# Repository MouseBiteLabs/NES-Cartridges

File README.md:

# NES-Cartridges
A collection of Nintendo Entertainment System (NES) cartridge circuit boards

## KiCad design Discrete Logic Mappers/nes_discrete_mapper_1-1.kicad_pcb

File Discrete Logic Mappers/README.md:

# Nintendo Entertainment System (NES) Discrete Mapper Cartridge

This is an updated design of my old <a href="https://mousebitelabs.com/2020/09/11/nes-reproduction-quick-guide-custom-pcb/">NES Discrete cartridge boards</a>. Functionally, this design is nearly the same as the older one, but I added compatibility for a few new mappers and expanded the available memory for some mapper types, and under the hood I have ported the project over from Eagle to KiCad and heavily cleaned up the schematic and some of the trace routings. This version is also fully open source!

This circuit board can be used to make most NES cartridges that rely on discrete logic chips to operate. These boards are most common in the earlier NES releases. The following mapper types are supported (click the link to view the games that use that specific mapper):

| Board        | Mapper | Example Game                  | Database Link                                                                                  |
| ------------ | ------ | ----------------------------- | ---------------------------------------------------------------------------------------------- |
| NROM         | 0      | Balloon Fight                 | [https://nescartdb.com/search/advanced?ines=0](https://nescartdb.com/search/advanced?ines=0)   |
| UxROM        | 2      | Castlevania                   | [https://nescartdb.com/search/advanced?ines=2](https://nescartdb.com/search/advanced?ines=2)   |
| CNROM        | 3      | Paperboy                      | [https://nescartdb.com/search/advanced?ines=3](https://nescartdb.com/search/advanced?ines=3)   |
| AxROM        | 7      | Battletoads                   | [https://nescartdb.com/search/advanced?ines=7](https://nescartdb.com/search/advanced?ines=7)   |
| Color Dreams | 11     | Bible Adventures              | [https://nescartdb.com/search/advanced?ines=11](https://nescartdb.com/search/advanced?ines=11) |
| BNROM        | 34     | Deadly Towers                 | [https://nescartdb.com/search/advanced?ines=34](https://nescartdb.com/search/advanced?ines=34) |
| GNROM        | 66     | Super Mario Bros. / Duck Hunt | [https://nescartdb.com/search/advanced?ines=66](https://nescartdb.com/search/advanced?ines=66) |

There are a handful of more obscure mappers supported as well:

| Board            | Mapper | Example Game        | Wiki Link                                                                                  |
| ---------------- | ------ | ------------------- | ------------------------------------------------------------------------------------------ |
| CNROM (Panesian) | 3      | Bubble Bath Babes   | https://www.nesdev.org/wiki/Oversize                                                       |
| NINA-03/-06      | 79     | Krazy Kreatures     | https://www.nesdev.org/wiki/NINA-003-006                                                   |
| JF-xx            | 87     | The Goonies (JPN)   | https://www.nesdev.org/wiki/INES_Mapper_087                                                |
| SA-008-A, 800008 | 148    | Tetris (Tengen)     | [https://www.nesdev.org/wiki/INES_Mapper_148](https://www.nesdev.org/wiki/INES_Mapper_148) |
| UNROM (Modified) | 180    | Crazy Climber (JPN) | [https://www.nesdev.org/wiki/INES_Mapper_180](https://www.nesdev.org/wiki/INES_Mapper_180) |

## For Replacing Damaged Circuit Boards

This board can be used as a drop-in replacement for damaged original NES cartridge circuit boards - **but only for NROM and CNROM games**. This means you can take the chips off of the damaged circuit boards (assuming the chips are still in good condition) and solder them into this board. You may need to replace the capacitors if they are damaged. **You still need to configure the board for the mapper you wish to use with the solder pads, and bend out pin 28 on the PRG Mask ROM, as <a href="https://github.com/MouseBiteLabs/NES-Cartridges/tree/main/Discrete%20Logic%20Mappers#board-configurations">detailed in the section below</a>**.

If you wish to use this board to replace damaged circuit boards for other mapper types (such as AxROM or UxROM), you can transfer over the logic chips and CIC, but will need to do some manual rewiring of the Mask ROM chips, which I will not be detailing in this repository. <a href="https://www.nesdev.org/wiki/Mask_ROM_pinout">Refer to this page on the Nesdev wiki</a> and cross-reference with <a href="https://github.com/MouseBiteLabs/NES-Cartridges/blob/main/Discrete%20Logic%20Mappers/schematic.pdf">board schematic</a> if you wish to figure it out for yourself. It will involve bending specific pins on the Mask ROM up so they are not inserted into the sockets on the board to be rewired elsewhere.

## Important Things Before You Start

1) <a href="https://github.com/MouseBiteLabs/NES-Cartridges/wiki">Please review the wiki for more information about using the circuit boards, instructions for how to program them, and example builds.</a>
2) When soldering parts on, it's a good idea to put kapton tape or otherwise cover the bottom cartridge edge. You do not want to get solder on the cartridge contacts.
3) I am not responsible for any damage you do to your self or your property. Attempt this project at your own risk.
4) I do not guarantee design compatibility. You may encounter issues with certain games. There is also a chance I have made an error in the design or the BOM - if this is the case, I will do everything I can to address the problem as quickly as possible.
5) If you are using this board to make games other than for personal use, you must have permission from the originator to use and distribute any ROM images or other related material. You are responsible for making sure you adhere to any license requirements.

DO NOT use my circuit boards for profiting from stolen work - this especially includes homebrew content, ROM hacks, and using fan-made labels without permission from the originator. **Support ALL original creators!**

## Board Characteristics and Order Information

The zipped folder contains all the gerber files for this board. The following options **must** be chosen when ordering boards for yourself.

- Thickness: 1.2mm
- Surface Finish: ENIG
- Gold Fingers: Yes, 30° chamfer

You can use the zipped folder at any board fabricator you like. You may also buy the board from PCBWay using this link (disclosure: I receive 10% of the sale value to go towards future PCB orders of my own):

### Purchase from My Website

You can purchase this circuit board at my website, [https://mousebitelabs.store](https://mousebitelabs.store). Click the following image to be directed to the specific item listing:

### Purchase from Etsy

I also offer the board on Etsy, if you would rather purchase through there - click the banner to be redirected.

## Required Equipment

- You will need basic tools, like a soldering iron.
- You need a way to program the ROM chip(s). For NES games, I usually use the <a href="https://xgecu.myshopify.com/products/xgecu-new-t48-tl866-3gprogrammer-v12-01-support-28000-ics-for-spi-nor-nand-flash-emmc-bga153-162-169-100-221-tsop-sop-plcc">T48 programmer</a>.
- If you do not have an original CIC to transfer to this board, or a region unlock mod on your console, you will need an ATTINY13 with the <a href="http://forums.nesdev.com/download/file.php?id=5943">AVRCIC code by krikzz</a> to fake out the lockout chip. You will need a way to program these chips. I use the T48 to do so, but you can also use something like the <a href="https://www.microchip.com/en-us/development-tool/pg164130">PICkit 3.</a> Be sure to see <a href="https://github.com/MouseBiteLabs/NES-Cartridges/wiki/Programming-the-CIC">the tutorial on how to program these lockout chips,</a> as you need to change a few settings before programming the code.

## How to Program the Game and CIC

For a tutorial on how to prepare and program the ROM file(s), <a href="https://github.com/MouseBiteLabs/NES-Cartridges/wiki/Programming-the-ROM-chips">please check out this wiki page.</a>

For a tutorial on how to program the CIC code onto the ATTINY13 if you do not have an original CIC to use, <a href="https://github.com/MouseBiteLabs/NES-Cartridges/wiki/Programming-the-CIC">please check out this wiki page.</a>

## Board Configurations

This board is highly customizable. You *do not* need every single part on this board to make a game. The cartridge configuration you need for the game you want to make is mainly dependent on the mapping type. Depending on your needs, you only need to solder on certain components, which you can find below in the BOM section. You will also need to configure the game with the various solder jumpers on the back of the board.

<a href="https://github.com/MouseBiteLabs/NES-Cartridges/wiki/Discrete-Mapper">**I highly recommend checking out the various examples of board configurations on the wiki.**</a>

### Solder Jumpers

This board is rife with solder jumpers. Sorry! That's the cost of making a single board that can cover many different configurations. Not all jumpers need to be soldered, depending on the game you're making. Again, <a href="https://github.com/MouseBiteLabs/NES-Cartridges/wiki/Discrete-Mapper">**I highly recommend checking out the various examples of board configurations on the wiki.**</a> That will give you a shortcut for most solder jumpers, other than the mirroring jumpers, which are detailed in this next section.

On the back of the board, you will see a legend for decoding what jumpers need to be soldered (this legend also tells you if you need ROM or RAM for the CHR component):

Basically, follow this for your selected mapper. Anywhere you see "A" next to a jumper, bridge it with solder for AxROM games; for BNROM, look for "B"; etc. The exception to this is NROM - this requires no solder jumpers to be soldered, except for the mirroring jumper and the ROM /OE jumpers on the front of the board (indicated by "OTHERS").

#### ROM /OE Selection Jumpers

On the bottom right-hand side of the front of the board, you will see two sets of two-way jumpers:

The "OTHERS" in this case refers to "other" mappers other than AxROM or UxROM (including NROM). 

Solder them like this for AxROM games:

And this for UxROM games:

And this for all other mappers:

### Mirroring Jumpers

These jumpers need to be set for every game EXCEPT for AxROM games (AMROM, ANROM, AN1ROM, and AOROM) which require you to NOT solder these pads. If you do not set these pads properly for non-AxROM games, you will experience graphical issues. If after you make a game and you *are* experience graphical issues, but gameplay still works, then it might be that you set these pads wrong.

Each non-AxROM game needs to be set for Horizontal (V) or Vertical (H) mirroring. Yes, I know the letters are flipped, and there is a reason for that, but I'm not going to spend time explaining the details behind it. The main thing you need to know is that if you're making a game and you use the FamiROM tool (that is explained in the <a href="https://github.com/MouseBiteLabs/NES-Cartridges/wiki/Programming-the-ROM-chips">ROM preparation section</a> of the wiki), it will report the ROM information on the box that pops up. Check the "mirroring" value. In this example, Elevator Action, it reports the mirroring as Horizontal.

Now, check out the PCB (courtesy of NesCartDB):

See that the "V" pads are bridged. This is why my board shows both the nomenclature FamiROM reports and the letter that appears on the original PCB for the games.

### Selecting U4

U4 is the main mapping chip for all board types except NROM (which does not need one). U4B and U4C are 74'161 that have four sets of I/O, and U4A is the 74'377 which has eight. These I/O are connected to the data pins (D0-D7). If you're making a CNROM or UxROM game, you can use a 74'161 in the U4B socket; if you're making AxROM or BNROM, you can use a 74'161 in the U4C socket.

If you use the 74HCT377, you can achieve an "expanded" version of CNROM, UxROM, AxROM, and BNROM. This expanded memory has no functionality for games that do not use it - this feature is more for developers to take advantage of. One exception to this is Panesian games - these utilize the expanded CNROM mapper type, and therefore require the 74'377.

If you want an easy option to cover all your bases without having to think too hard about what chip to use, I recommend simply populating U4A (74HCT377).

### PRG ROM Considerations

I use the 39SF040 NOR Flash chips for all my ROM needs - they're new, easily available, and cover all your bases for NES games - but there are plenty of other options that can be used, like the 27C UV EPROMs (27C256, 27C512, 27C010, 27C020, 27C040, and 27C080). Whatever chip you select, it must be large enough to hold your ROM file (again, see the <a href="https://github.com/MouseBiteLabs/NES-Cartridges/wiki/Programming-the-ROM-chips">ROM preparation section</a> of the wiki). 

If you use the 27C040 or 27C080, then you need to solder these pads on the back:

If your ROM chip is only 28 pins (like 27C256 and 27C512, **or the original PRG Mask ROM if you are using the board as an NROM or CNROM replacement**) you need to bend out pin 28 and solder it to the alternate hole labeled DIP28, shown here:

### Special Mapper Types

There are a few special cases for a few obscure mapper types that this board supports:
- For making Panesian games, follow instructions for a CNROM board type, but you must use U4A.
- To achieve Mapper 180, follow instructions for a UxROM board type, but replace the 74'32 with a 74'08. See the BOM for more information.
- To achieve Mapper 87, follow instructions for a CNROM board type, but you must use U4A with pins 5 and 6 bent out to solder to the adjacent pins from the U4B footprint.
- To achieve Mapper 79 or 148, follow instructions for a CNROM board type, but you must use U4B with pin 11 bent inward under the part footprint to solder to the test point.

Once again, again, <a href="https://github.com/MouseBiteLabs/NES-Cartridges/wiki/Discrete-Mapper">**I highly recommend checking out the various examples of board configurations on the wiki**</a> where this is also covered.

## Troubleshooting

<a href="https://github.com/MouseBiteLabs/NES-Cartridges/wiki/Troubleshooting-Tips">Please check out the wiki pages for troubleshooting tips.</a>

## Bill of Materials (BOM)

NOTE 1: The 39SF040 is listed as the recommended part for all of the following BOMs - it will cover any and all games, but you can also use the following chips if they are big enough for the game file you have:
- UV EPROM: 27C256, 27C512, 27C010, 27C020, 27C040, 27C080
- NOR Flash: 39SF512, 39SF010, 39SF020 

NOTE 2: The AS6C6264 is recommended for the CHR RAM for boards that require it, but the AS6C62256 also works.

All games will require the following parts:

| Reference | Value/Part Number | Package        | Description                     | Source                                           |
| --------- | ----------------- | -------------- | ------------------------------- | ------------------------------------------------ |
| U1 \*     | CIC / ATTINY13  | DIP-16 / DIP-8 | Region Lockout Chip             | [https://mou.sr/4h4SnUi](https://mou.sr/4h4SnUi) |
| U2        | 39SF040        | DIP-32         | PRG ROM                         | [https://mou.sr/47odNbz](https://mou.sr/47odNbz) |
| CC        | 22uF              | 5mm x 5mm      | Aluminum Electrolytic Capacitor | [https://mou.sr/4moiXKK](https://mou.sr/4moiXKK) |
| C1        | 0.1uF             | Radial, 5mm    | Capacitor (MLCC)                | [https://mou.sr/4mvAwIR](https://mou.sr/4mvAwIR) |
| C2        | 0.1uF             | Radial, 5mm    | Capacitor (MLCC)                | [https://mou.sr/4mvAwIR](https://mou.sr/4mvAwIR) |
| R8 \*\*   | 100k              | Axial, 3.3mm   | Resistor                        | [https://mou.sr/3NOD0De](https://mou.sr/3NOD0De) |

\* This can be harvested from an original NES game (this is not needed if you have region modded your NES)

\*\* Not needed if U2 is a 28-pin UV EPROM.

### NROM

These extra parts are required for NROM games:

| Reference | Value/Part Number | Package     | Description      | Source                                           |
| --------- | ----------------- | ----------- | ---------------- | ------------------------------------------------ |
| U3        | 39SF040           | DIP-32      | CHR ROM          | [https://mou.sr/47odNbz](https://mou.sr/47odNbz) |
| C3        | 0.1uF             | Radial, 5mm | Capacitor (MLCC) | [https://mou.sr/4mvAwIR](https://mou.sr/4mvAwIR) |

### UxROM

These extra parts are required for UNROM and UOROM games:

| Reference | Value/Part Number | Package     | Description      | Source                                           |
| --------- | ----------------- | ----------- | ---------------- | ------------------------------------------------ |
| U3        | AS6C6264          | DIP-28      | CHR RAM          | [https://mou.sr/3KQ1Tv5](https://mou.sr/3KQ1Tv5) |
| U4A \*    | 74HCT377          | DIP-20      | Octal Flip-Flop  | [https://mou.sr/4ozFyER](https://mou.sr/4ozFyER) |
| U4B \*    | 74HCT161          | DIP-16      | Binary Counter   | [https://mou.sr/4qlCT3n](https://mou.sr/4qlCT3n) |
| U5        | 74HCT32           | DIP-14      | Quad 2-in OR     | [https://mou.sr/471nOwi](https://mou.sr/471nOwi) |
| C3        | 0.1uF             | Radial, 5mm | Capacitor (MLCC) | [https://mou.sr/4mvAwIR](https://mou.sr/4mvAwIR) |
| C4A \*    | 0.1uF             | Radial, 5mm | Capacitor (MLCC) | [https://mou.sr/4mvAwIR](https://mou.sr/4mvAwIR) |
| C4B \*    | 0.1uF             | Radial, 5mm | Capacitor (MLCC) | [https://mou.sr/4mvAwIR](https://mou.sr/4mvAwIR) |
| C5        | 0.1uF             | Radial, 5mm | Capacitor (MLCC) | [https://mou.sr/4mvAwIR](https://mou.sr/4mvAwIR) |

\* Use either U4A/C4A *OR* U4B/C4B. Do not use both!

Special note: For Mapper 180, replace U5 with 74HCT08 ([https://mou.sr/3AM08eK](https://mou.sr/3AM08eK))

### CNROM

These extra parts are required for CNROM games:

| Reference | Value/Part Number | Package     | Description      | Source                                           |
| --------- | ----------------- | ----------- | ---------------- | ------------------------------------------------ |
| U3        | 39SF040           | DIP-32      | CHR ROM          | [https://mou.sr/47odNbz](https://mou.sr/47odNbz) |
| U4A \*    | 74HCT377          | DIP-20      | Octal Flip-Flop  | [https://mou.sr/4ozFyER](https://mou.sr/4ozFyER) |
| U4B \*    | 74HCT161          | DIP-16      | Binary Counter   | [https://mou.sr/4qlCT3n](https://mou.sr/4qlCT3n) |
| C3        | 0.1uF             | Radial, 5mm | Capacitor (MLCC) | [https://mou.sr/4mvAwIR](https://mou.sr/4mvAwIR) |
| C4A \*    | 0.1uF             | Radial, 5mm | Capacitor (MLCC) | [https://mou.sr/4mvAwIR](https://mou.sr/4mvAwIR) |
| C4B \*    | 0.1uF             | Radial, 5mm | Capacitor (MLCC) | [https://mou.sr/4mvAwIR](https://mou.sr/4mvAwIR) |

\* Use either U4A/C4A *OR* U4B/C4B. Do not use both!

Special note: Panesian and Mapper 87 games require U4A/C4A, Mapper 79 and 149 games require U4B/C4B.

### AxROM

These extra parts are required for AMROM, ANROM, AN1ROM, and AOROM games:

| Reference | Value/Part Number | Package     | Description      | Source                                           |
| --------- | ----------------- | ----------- | ---------------- | ------------------------------------------------ |
| U3        | AS6C6264          | DIP-28      | CHR RAM          | [https://mou.sr/3KQ1Tv5](https://mou.sr/3KQ1Tv5) |
| U4A \*    | 74HCT377          | DIP-20      | Octal Flip-Flop  | [https://mou.sr/4ozFyER](https://mou.sr/4ozFyER) |
| U4C \*    | 74HCT161          | DIP-16      | Binary Counter   | [https://mou.sr/4qlCT3n](https://mou.sr/4qlCT3n) |
| U6        | 74HCT02           | DIP-14      | Quad 2-in NOR    | [https://mou.sr/4qo4i4z](https://mou.sr/4qo4i4z) |
| C3        | 0.1uF             | Radial, 5mm | Capacitor (MLCC) | [https://mou.sr/4mvAwIR](https://mou.sr/4mvAwIR) |
| C4A \*    | 0.1uF             | Radial, 5mm | Capacitor (MLCC) | [https://mou.sr/4mvAwIR](https://mou.sr/4mvAwIR) |
| C4C \*    | 0.1uF             | Radial, 5mm | Capacitor (MLCC) | [https://mou.sr/4mvAwIR](https://mou.sr/4mvAwIR) |
| C6        | 0.1uF             | Radial, 5mm | Capacitor (MLCC) | [https://mou.sr/4mvAwIR](https://mou.sr/4mvAwIR) |

\* Use either U4A/C4A *OR* U4C/C4C. Do not use both!

### Color Dreams

These extra parts are required for Color Dreams games:

| Reference | Value/Part Number | Package     | Description      | Source                                           |
| --------- | ----------------- | ----------- | ---------------- | ------------------------------------------------ |
| U3        | 39SF040           | DIP-32      | CHR ROM          | [https://mou.sr/47odNbz](https://mou.sr/47odNbz) |
| U4A       | 74HCT377          | DIP-20      | Octal Flip-Flop  | [https://mou.sr/4ozFyER](https://mou.sr/4ozFyER) |
| C3        | 0.1uF             | Radial, 5mm | Capacitor (MLCC) | [https://mou.sr/4mvAwIR](https://mou.sr/4mvAwIR) |
| C4A       | 0.1uF             | Radial, 5mm | Capacitor (MLCC) | [https://mou.sr/4mvAwIR](https://mou.sr/4mvAwIR) |

### BNROM

These extra parts are required for BNROM games:

| Reference | Value/Part Number | Package     | Description      | Source                                           |
| --------- | ----------------- | ----------- | ---------------- | ------------------------------------------------ |
| U3        | AS6C6264          | DIP-28      | CHR RAM          | [https://mou.sr/3KQ1Tv5](https://mou.sr/3KQ1Tv5) |
| U4A \*    | 74HCT377          | DIP-20      | Octal Flip-Flop  | [https://mou.sr/4ozFyER](https://mou.sr/4ozFyER) |
| U4C \*    | 74HCT161          | DIP-16      | Binary Counter   | [https://mou.sr/4qlCT3n](https://mou.sr/4qlCT3n) |
| C3        | 0.1uF             | Radial, 5mm | Capacitor (MLCC) | [https://mou.sr/4mvAwIR](https://mou.sr/4mvAwIR) |
| C4A \*    | 0.1uF             | Radial, 5mm | Capacitor (MLCC) | [https://mou.sr/4mvAwIR](https://mou.sr/4mvAwIR) |
| C4C \*    | 0.1uF             | Radial, 5mm | Capacitor (MLCC) | [https://mou.sr/4mvAwIR](https://mou.sr/4mvAwIR) |

\* Use either U4A/C4A *OR* U4C/C4C. Do not use both!

### GNROM

These extra parts are required for GNROM games:

| Reference | Value/Part Number | Package     | Description      | Source                                           |
| --------- | ----------------- | ----------- | ---------------- | ------------------------------------------------ |
| U3        | 39SF040           | DIP-32      | CHR ROM          | [https://mou.sr/47odNbz](https://mou.sr/47odNbz) |
| U4A       | 74HCT377          | DIP-20      | Octal Flip-Flop  | [https://mou.sr/4ozFyER](https://mou.sr/4ozFyER) |
| C3        | 0.1uF             | Radial, 5mm | Capacitor (MLCC) | [https://mou.sr/4mvAwIR](https://mou.sr/4mvAwIR) |
| C4A       | 0.1uF             | Radial, 5mm | Capacitor (MLCC) | [https://mou.sr/4mvAwIR](https://mou.sr/4mvAwIR) |

## Sprite Glitch Resistors

In rare cases, you might encounter some sprite glitching even if everything is configured properly. This usually only happens when you have things like a Famicom-NES adapter or Game Genie in your system that artificially lengthen the connections from the cartridge to the console. It also can depend on the type of console you're using. What sets this aside from other graphical glitches is that it affects the sprites, not the entire screen. So if you’re getting strange palettes, missing backgrounds, or weird tiles, your problem is something else, probably a bad cartridge connector or dirty cartridge edge. What you’ll see if you’re getting this kind of error, known as OAM corruption, looks something like this (click the picture to view a video):

Fixing this error involves adding ~100 ohm resistors (like these: https://mou.sr/4o1seJo) in series with the PRG D0 to D7 lines. This can be done by cutting the exposed traces in the middle of RD0 to RD7 with a blade, and soldering resistors in place (surface mount size 0603). Be careful not to cut other parts of the board (or yourself).

(These pictures are from another board, but they are present on this board as well.)

## Considerations for v1.0

On v1.0, mapper 79 and 148 are not supported. (That shouldn't affect most users)

If you are using a 27C040 or 27C080 for the PRG ROM, you must bend up pin 1 before placing it into the PRG socket. Then, solder a wire from the bent-up pin and connect it to pin 31.

## Revision History

### v1.1 - Release

- Added pad for using 27C040 and 27C080 PRG EPROMs.
- Fixed Mapper 079/148 instructions and added extra test point for proper configuration.

### v1.0 - Prototype

## Acknowledgements and Resources

- The <a href="https://www.nesdev.org/wiki/Nesdev_Wiki">Nesdev wiki</a> was *indispensible* for making this board, especially <a href="https://www.nesdev.org/wiki/User:Lidnariq/Discrete_Logic_Table">this specific page</a> by lidnariq.
- <a href="https://nescartdb.com/">NesCartDB</a> has a wealth of images and information about the vast majority of the NES library. I've used it for years, it helped me create these boards, and I suggest you do too for referencing specific games.
- Continual thanks to all in the nesdev community for their resources, design tips, and support throughout the past half-decade.

## License

<br />This work is licensed under a <a rel="license" href="http://creativecommons.org/licenses/by-sa/4.0/">Creative Commons Attribution-ShareAlike 4.0 International License</a>. You are able to copy and redistribute the material in any medium or format, as well as remix, transform, or build upon the material for any purpose (even commercial) - but you **must** give appropriate credit, provide a link to the license, and indicate if any changes were made.

©MouseBiteLabs 2025

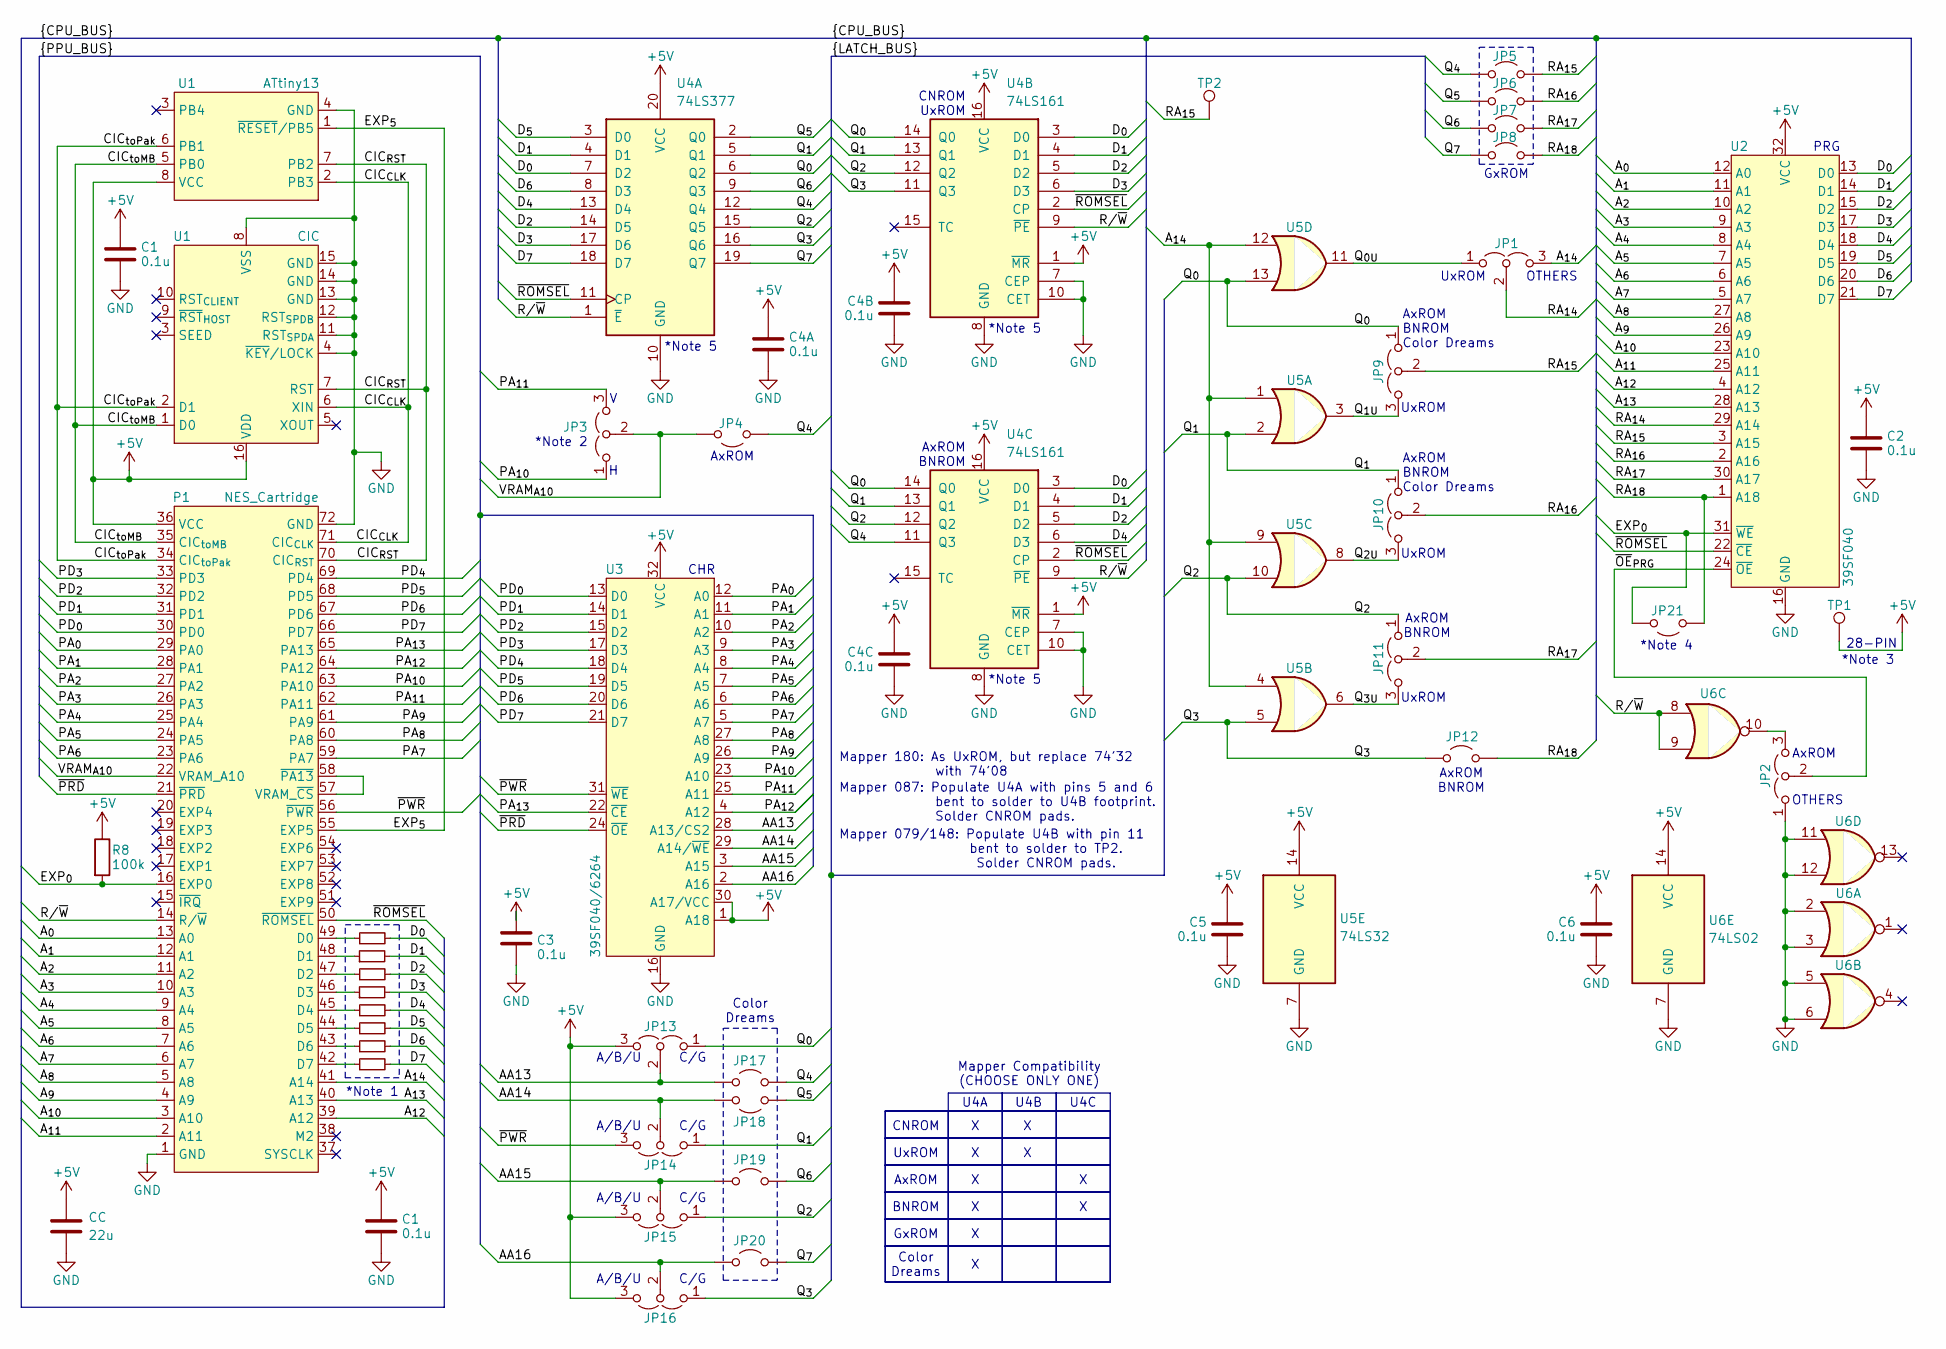
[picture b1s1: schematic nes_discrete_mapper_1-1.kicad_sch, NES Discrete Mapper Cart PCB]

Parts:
C1, C2, C3, C4A, C4B, C4C, C5, C6: 0.1u; THT_SMT_0803_SHORT
CC: 22u; CP_Radial_D5.0mm_P2.50mm
JP1, JP2, JP3, JP9, JP10, JP11, JP13, JP14, JP15, JP16: Jumper_3_Open; SJ_2
JP4, JP5, JP6, JP7, JP8, JP12, JP17, JP18, JP19, JP20, JP21: Jumper_2_Open; SJ
P1: NES_Cartridge; Cart_Edge_NES_72
R0, R1, R2, R3, R4, R5, R6, R7: R_Small; R_0603_1608Metric_Boxed_SHORTED
R8: 100k; THT_SMT_0803
TP1, TP2: TestPoint; TestPoint_THTPad_D1.5mm_Drill0.7mm
U1: CIC; DIP-16_W7.62mm
U2: 39SF040; DIP-32_W15.24mm
U3: 39SF040/6264; DIP-32_W15.24mm
U4A: 74LS377; DIP-20_W7.62mm
U4B, U4C: 74LS161; DIP-16_W7.62mm
U5: 74LS32; DIP-14_W7.62mm
U6: 74LS02; DIP-14_W7.62mm

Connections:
+5V: C1.1, C2.1, C3.1, C4A.1, C4B.1, C4C.1, C5.1, C6.1, CC.1, JP13.3 (B), JP15.3 (B), JP16.3 (B), P1.36 (VCC), R8.1, TP1.1, U1.8 (VCC), U1.16 (VDD), U2.32 (VCC), U3.1 (A18), U3.30 (A17/VCC), U3.32 (VCC), U4A.20 (VCC), U4B.1 (~MR), U4B.16 (VCC), U4C.1 (~MR), U4C.16 (VCC), U5.14 (VCC), U6.14 (VCC); also elsewhere on the board
/AA13: JP13.2 (C), JP17.1 (A), U3.28 (A13/CS2)
/AA14: JP14.2 (C), JP18.1 (A), U3.29 (A14/~WE)
/AA15: JP15.2 (C), JP19.1 (A), U3.3 (A15)
/AA16: JP16.2 (C), JP20.1 (A), U3.2 (A16)
/A_{0}: P1.13 (A0), U2.12 (A0)
/A_{1}: P1.12 (A1), U2.11 (A1)
/A_{2}: P1.11 (A2), U2.10 (A2)
/A_{3}: P1.10 (A3), U2.9 (A3)
/A_{4}: P1.9 (A4), U2.8 (A4)
/A_{5}: P1.8 (A5), U2.7 (A5)
/A_{6}: P1.7 (A6), U2.6 (A6)
/A_{7}: P1.6 (A7), U2.5 (A7)
/A_{8}: P1.5 (A8), U2.27 (A8)
/A_{9}: P1.4 (A9), U2.26 (A9)
/A_{10}: P1.3 (A10), U2.23 (A10)
/A_{11}: P1.2 (A11), U2.25 (A11)
/A_{12}: P1.39 (A12), U2.4 (A12)
/A_{13}: P1.40 (A13), U2.28 (A13)
/A_{14}: JP1.3 (B), P1.41 (A14), U5.1, U5.4, U5.9, U5.12
/CIC_{CLK}: P1.71 (CIC_{CLK}), U1.2 (PB3), U1.6 (PB1); also elsewhere on the board
/CIC_{RST}: P1.70 (CIC_{RST}), U1.7 (PB2); also elsewhere on the board
/CIC_{toMB}: P1.35 (CIC_{toMB}), U1.1 (~RESET/PB5), U1.5 (PB0); also elsewhere on the board
/CIC_{toPak}: P1.34 (CIC_{toPak}), U1.2 (PB3), U1.6 (PB1); also elsewhere on the board
/D_{0}: R0.2, U2.13 (D0), U4A.7 (D2), U4B.3 (D0), U4C.3 (D0)
/D_{1}: R1.2, U2.14 (D1), U4A.4 (D1), U4B.4 (D1), U4C.4 (D1)
/D_{2}: R2.2, U2.15 (D2), U4A.14 (D5), U4B.5 (D2), U4C.5 (D2)
/D_{3}: R3.2, U2.17 (D3), U4A.17 (D6), U4B.6 (D3)
/D_{4}: R4.2, U2.18 (D4), U4A.13 (D4), U4C.6 (D3)
/D_{5}: R5.2, U2.19 (D5), U4A.3 (D0)
/D_{6}: R6.2, U2.20 (D6), U4A.8 (D3)
/D_{7}: R7.2, U2.21 (D7), U4A.18 (D7)
/EXP_{0}: JP21.1 (A), P1.16 (EXP0), R8.2, U2.31 (~WE)
/EXP_{5}: P1.55 (EXP5), U1.1 (~RESET/PB5); also elsewhere on the board
/PA_{0}: P1.29 (PA0), U3.12 (A0)
/PA_{1}: P1.28 (PA1), U3.11 (A1)
/PA_{2}: P1.27 (PA2), U3.10 (A2)
/PA_{3}: P1.26 (PA3), U3.9 (A3)
/PA_{4}: P1.25 (PA4), U3.8 (A4)
/PA_{5}: P1.24 (PA5), U3.7 (A5)
/PA_{6}: P1.23 (PA6), U3.6 (A6)
/PA_{7}: P1.59 (PA7), U3.5 (A7)
/PA_{8}: P1.60 (PA8), U3.27 (A8)
/PA_{9}: P1.61 (PA9), U3.26 (A9)
/PA_{10}: JP3.1 (A), P1.63 (PA10), U3.23 (A10)
/PA_{11}: JP3.3 (B), P1.62 (PA11), U3.25 (A11)
/PA_{12}: P1.64 (PA12), U3.4 (A12)
/PA_{13}: P1.65 (PA13), U3.22 (~CE)
/PD_{0}: P1.30 (PD0), U3.13 (D0)
/PD_{1}: P1.31 (PD1), U3.14 (D1)
/PD_{2}: P1.32 (PD2), U3.15 (D2)
/PD_{3}: P1.33 (PD3), U3.17 (D3)
/PD_{4}: P1.69 (PD4), U3.18 (D4)
/PD_{5}: P1.68 (PD5), U3.19 (D5)
/PD_{6}: P1.67 (PD6), U3.20 (D6)
/PD_{7}: P1.66 (PD7), U3.21 (D7)
/Q_{0U}: JP1.1 (A), U5.11
/Q_{0}: JP9.1 (A), JP13.1 (A), U4A.6 (Q2), U4B.14 (Q0), U4C.14 (Q0), U5.13
/Q_{1U}: JP9.3 (B), U5.3
/Q_{1}: JP10.1 (A), JP14.1 (A), U4A.5 (Q1), U4B.13 (Q1), U4C.13 (Q1), U5.2
/Q_{2U}: JP10.3 (B), U5.8
/Q_{2}: JP11.1 (A), JP15.1 (A), U4A.15 (Q5), U4B.12 (Q2), U4C.12 (Q2), U5.10
/Q_{3U}: JP11.3 (B), U5.6
/Q_{3}: JP12.2 (B), JP16.1 (A), U4A.16 (Q6), U4B.11 (Q3), U5.5
/Q_{4}: JP4.2 (B), JP5.1 (A), JP17.2 (B), U4A.12 (Q4), U4C.11 (Q3)
/Q_{5}: JP6.1 (A), JP18.2 (B), U4A.2 (Q0)
/Q_{6}: JP7.1 (A), JP19.2 (B), U4A.9 (Q3)
/Q_{7}: JP8.1 (A), JP20.2 (B), U4A.19 (Q7)
/RA_{14}: JP1.2 (C), U2.29 (A14)
/RA_{15}: JP5.2 (B), JP9.2 (C), TP2.1, U2.3 (A15)
/RA_{16}: JP6.2 (B), JP10.2 (C), U2.2 (A16)
/RA_{17}: JP7.2 (B), JP11.2 (C), U2.30 (A17)
/RA_{18}: JP8.2 (B), JP12.1 (A), JP21.2 (B), U2.1 (A18)
/R/~W: P1.14 (R/~W), U4A.1 (~E), U4B.9 (~PE), U4C.9 (~PE), U6.8, U6.9
/VRAM_{A10}: JP3.2 (C), JP4.1 (A), P1.22 (VRAM_A10)
/~OE_{PRG}: JP2.2 (C), U2.24 (~OE)
/~PRD: P1.21 (~PRD), U3.24 (~OE)
/~PWR: JP14.3 (B), P1.56 (~PWR), U3.31 (~WE)
/~ROMSEL: P1.50 (~ROMSEL), U2.22 (~CE), U4A.11 (CP), U4B.2 (CP), U4C.2 (CP)
GND: C1.2, C2.2, C3.2, C4A.2, C4B.2, C4C.2, C5.2, C6.2, CC.2, JP2.1 (A), P1.1 (GND), P1.72 (GND), U1.4 (GND), U1.8 (VCC), U1.11 (RST_{SPDA}), U1.12 (RST_{SPDB}), U1.13 (GND), U1.14 (GND), U1.15 (GND), U2.16 (GND), U3.16 (GND), U4A.10 (GND), U4B.7 (CEP), U4B.8 (GND), U4B.10 (CET), U4C.7 (CEP), U4C.8 (GND), U4C.10 (CET), U5.7 (GND), U6.2, U6.3, U6.5, U6.6, U6.7 (GND), U6.11, U6.12; also elsewhere on the board
unnamed: JP2.3 (B), U6.10
unnamed: P1.49 (D0), R0.1
unnamed: P1.48 (D1), R1.1
unnamed: P1.47 (D2), R2.1
unnamed: P1.46 (D3), R3.1
unnamed: P1.45 (D4), R4.1
unnamed: P1.44 (D5), R5.1
unnamed: P1.43 (D6), R6.1
unnamed: P1.42 (D7), R7.1
unnamed: P1.57 (VRAM_~CS), P1.58 (~PA13)

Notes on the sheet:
A/B/U
AxROM BNROM Color Dreams
UxROM
AxROM
AxROM BNROM
GxROM
*Note 3
BNROM
*Note 1
Mapper 180: As UxROM, but replace 74'32 with 74'08
OTHERS
Mapper 079/148: Populate U4B with pin 11 bent to solder to TP2. Solder CNROM pads.
CNROM UxROM
*Note 5
C/G
Mapper Compatibility (CHOOSE ONLY ONE)
*Note 4
Mapper 087: Populate U4A with pins 5 and 6 bent to solder to U4B footprint. Solder CNROM pads.
U4A U4B U4C
*Note 2
28-PIN
CNROM
CHR
PRG
Color Dreams

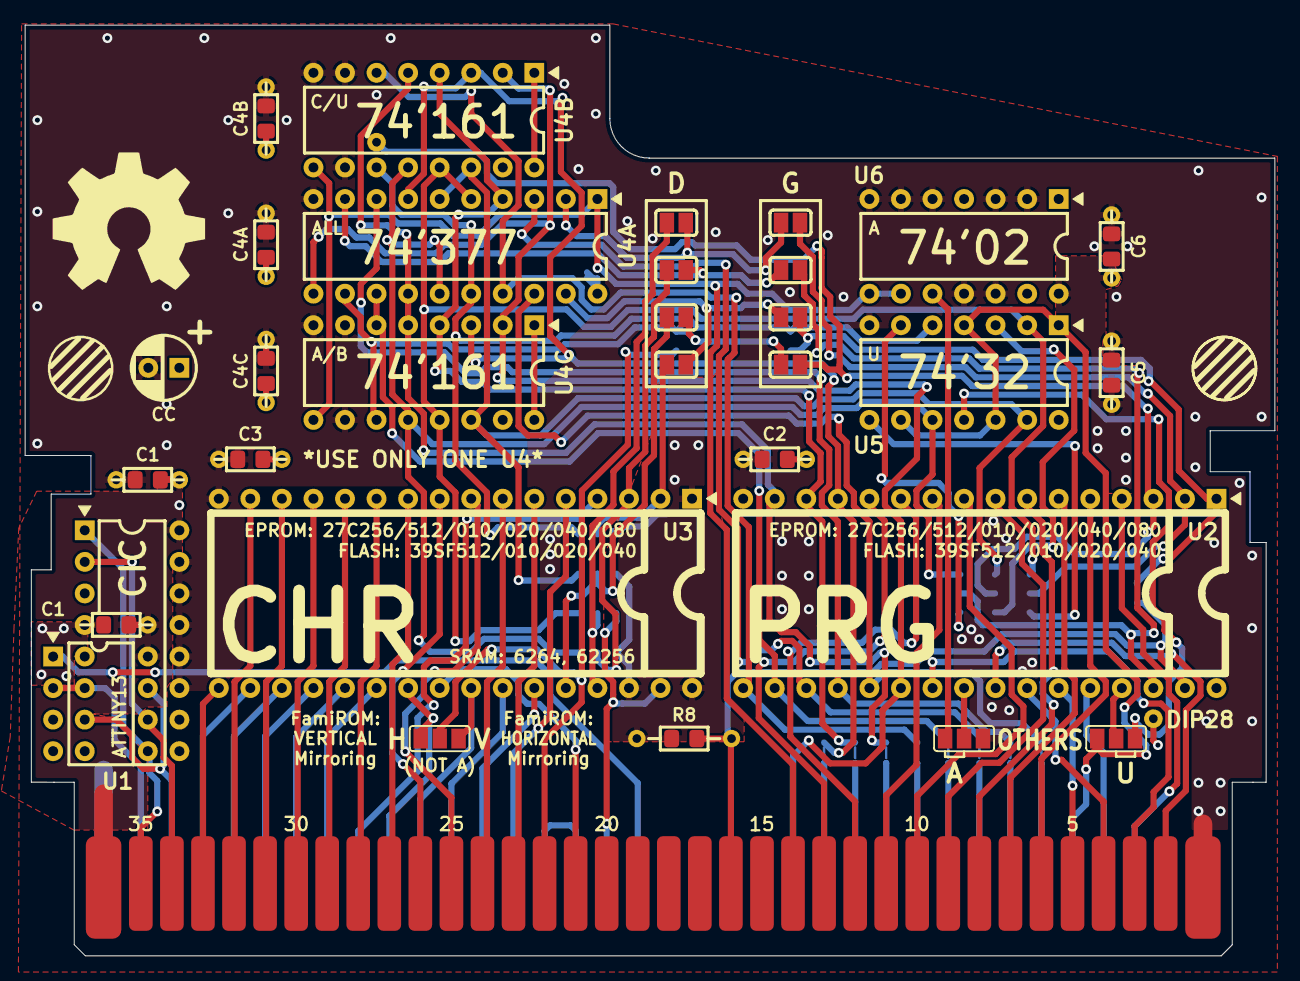
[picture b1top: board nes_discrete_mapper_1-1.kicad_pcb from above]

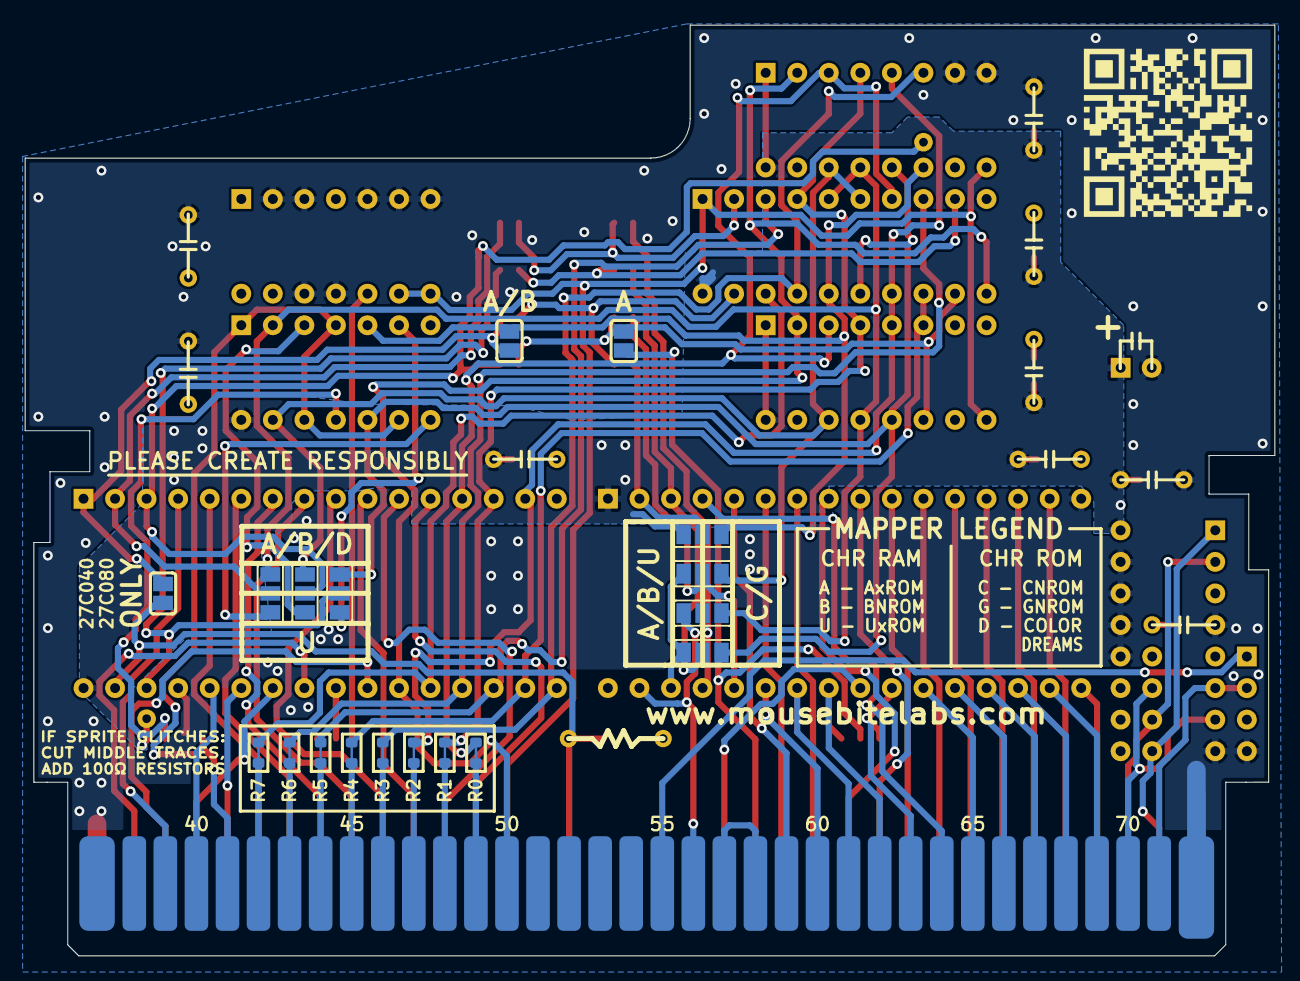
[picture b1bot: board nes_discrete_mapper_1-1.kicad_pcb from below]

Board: 2 copper layers, 100.6 x 74.9 mm, 52 parts (18 on the bottom side), 90 nets.

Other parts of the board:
C1#2: 0.1u; THT_SMT_0803_SHORT
U1A1: CIC; DIP-16_W7.62mm
U1B1: ATtiny13; DIP-8_W7.62mm

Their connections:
+5V: C1#2.1, U1A1.16 (VDD), U1B1.8 (VCC); also elsewhere on the board
/CIC_{CLK}: U1A1.6 (XIN), U1B1.2 (PB3); also elsewhere on the board
/CIC_{RST}: U1A1.7 (RST), U1B1.7 (PB2); also elsewhere on the board
/CIC_{toMB}: U1A1.1 (D0), U1B1.5 (PB0); also elsewhere on the board
/CIC_{toPak}: U1A1.2 (D1), U1B1.6 (PB1); also elsewhere on the board
/EXP_{5}: U1B1.1 (~RESET/PB5); also elsewhere on the board
GND: C1#2.2, U1A1.4 (~KEY/LOCK), U1A1.8 (VSS), U1A1.11 (RST_{SPDA}), U1A1.12 (RST_{SPDB}), U1A1.13 (GND), U1A1.14 (GND), U1A1.15 (GND), U1B1.4 (GND); also elsewhere on the board

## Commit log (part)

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2025-07-05 Create Mapper 30 (NESmaker)

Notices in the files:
Discrete Logic Mappers/README.md:
This work is licensed under a Creative Commons Attribution-ShareAlike 4.0 International License. You are able to copy and redistribute the material in any medium or format, as well as remix, transform, or build upon the material for any purpose (even commercial) - but you **must** give appropriate credit, provide a link t
©MouseBiteLabs 2025
